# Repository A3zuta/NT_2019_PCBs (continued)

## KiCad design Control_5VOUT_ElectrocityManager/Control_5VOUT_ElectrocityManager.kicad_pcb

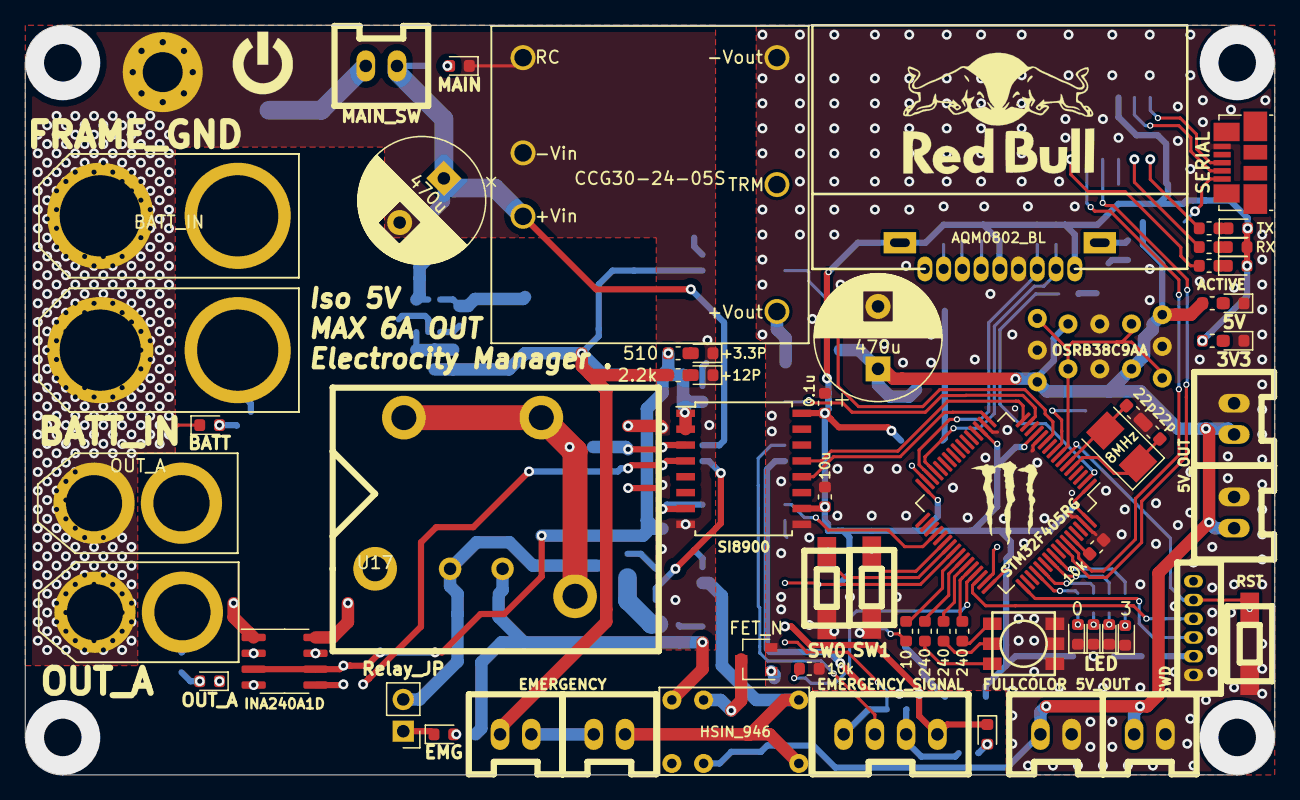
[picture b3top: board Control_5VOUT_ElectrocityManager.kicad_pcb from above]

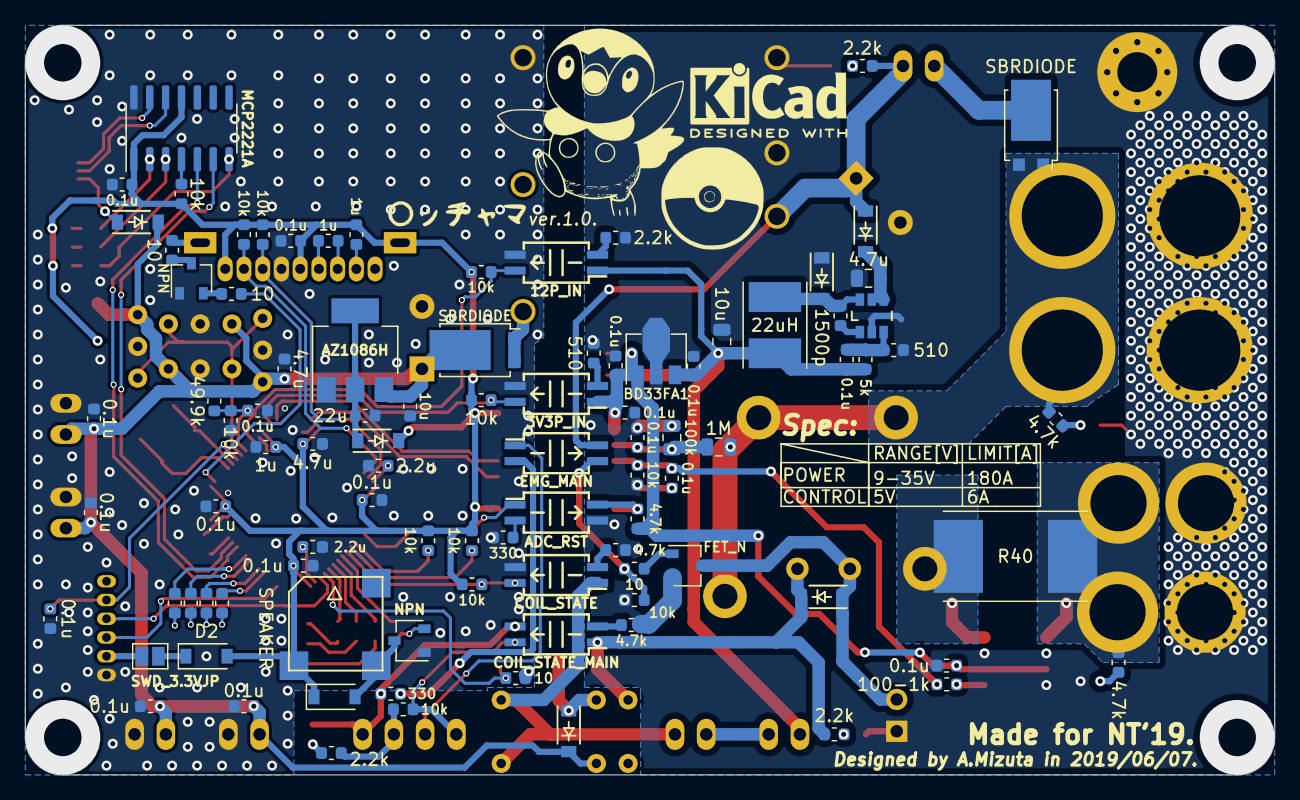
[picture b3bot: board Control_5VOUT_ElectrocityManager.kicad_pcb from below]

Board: 2 copper layers, 100.0 x 60.0 mm, 171 parts (100 on the bottom side), 107 nets.

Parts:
C1, C2: 22p; C_0603_1608Metric
C3, C5, C7, C9, C10, C12, C18, C19, C21, C24, C25, C27, C30, C31, C32, C34, C35, C36, C37: 0.1u; C_0603_1608Metric
C4, C6: 470u; CP_Radial_D10.0mm_P5.00mm
C8, C17: 4.7u; C_0603_1608Metric
C11, C13: 2.2u; C_0603_1608Metric
C14, C26: 10u; C_0603_1608Metric
C15, C22, C23: 1u; C_0603_1608Metric
C16: 22u; C_0603_1608Metric
C28: 1500p; C_0603_1608Metric
C29: 4.7u; C_0805_2012Metric
C33: 10u; C_0805_2012Metric
D1, D2: DIODE; D_SOD-123
D3: TX; LED_0603_1608Metric
D4: RX; LED_0603_1608Metric
D5: ACTIVE; LED_0603_1608Metric
D6, D9: SBRDIODE; TO-277B
D7, D8, D10, D17, D19, D20: DIODE; SOD-123
D11: LED0; LED_0603_1608Metric
D12: LED1; LED_0603_1608Metric
D13: LED2; LED_0603_1608Metric
D14: LED3; LED_0603_1608Metric
D15: 5V; LED_0603_1608Metric
D16: 3V3; LED_0603_1608Metric
D18: MAIN; LED_0603_1608Metric
D21: +3.3P; LED_0603_1608Metric
D22: +12P; LED_0603_1608Metric
D23: BATT; LED_0603_1608Metric
D24: LED; LED_0603_1608Metric
D25: EMG; LED_0603_1608Metric
D26: OUT_A; LED_0603_1608Metric
JP1: SWD_3.3VJP; SolderJumper-2_P1.3mm_Open_Pad1.0x1.5mm
JP2: Relay_JP; PinHeader_1x02_P2.54mm_Vertical
L1: 22uH; L_Taiyo-Yuden_NR-50xx_HandSoldering
LOGO1: OPEN_HARDWARE_1; KiCad-Logo2_5mm_SilkScreen
P1: SWD; ZH_6P
P2: SERIAL; USB_Micro-B_Molex_47346-0001
P3, P5: BATT_IN; XT90PB
P4, P6: OUT_A; XT60_F
P7: MAIN_SW; XA_2P
P8, P9: EMERGENCY; XA_2P
P10: EMERGENCY_SIGNAL; XA_4P
P11: FRAME_GND; MountingHole_3.2mm_M3_Pad_Via
P12, P13, P14, P15: 5V_OUT; XA_2P
Q1, Q4: NPN; SOT-23W
Q2, Q3: FET_N; SOT-23W
R1, R10, R13, R16, R18: 10; R_0603_1608Metric
R2, R32, R47, R48: 510; R_0603_1608Metric
R3, R6, R9, R11, R12, R14, R15, R23, R30, R33, R35, R43, R46, R51: 10k; R_0603_1608Metric
R4, R5, R7, R17, R19, R22, R24, R26, R31, R36: 330; R_0603_1608Metric
R8: 49.9k; R_0603_1608Metric
R20, R37, R39, R49, R52: 2.2k; R_0603_1608Metric
R21, R25, R41, R50, R53: 4.7k; R_0603_1608Metric
R27, R28, R29: 240; R_0603_1608Metric
R34: 5k; R_0603_1608Metric
R40: R; R_Shunt_Vishay_WSR2_WSR3
R42: 100-1k; R_0603_1608Metric
R44: 1M; R_0805_2012Metric
R45: 100k; R_0805_2012Metric
SP1: SPEAKER; UGCT7525AN4
SW1: RESET; SMD_Button
SW2: SW0; SMD_Button
SW3: SW1; SMD_Button
U1: CCG30-24-05S; CCG30-24-xxS
U2: MCP2221A; SOIC-14_3.9x8.7mm_P1.27mm
U3: STM32F405RG; LQFP-64_10x10mm_P0.5mm
U4: AZ1086H; SOT-223-3_TabPin2
U5, U7, U9: OSRB38C9AA-Miz; OSRB38C9AA
U6: OSRB38C9AA
U8: HSIN_946; relay_HSINDA_Y14H
U10: EMG_MAIN; SOIJ-4_5.3x5.3mm_Pitch1.27mm
U11: ADC_RST; SOIJ-4_5.3x5.3mm_Pitch1.27mm
U12: AQM0802_BL; AQM0802_BackLight
U13: 12P_IN; SOIJ-4_5.3x5.3mm_Pitch1.27mm
U14: COIL_STATE; SOIJ-4_5.3x5.3mm_Pitch1.27mm
U15: SI8900; Si8900
U16: FULLCOLOR; OSTBABS4C2B
U17: RELAY; V23076-A3001-D142
U18: LOGO; Power_logo_Silk_5x5
U19: BD9G101G; TSOT-6-MK06A
U20: BD33FA1; SOT-89-3
U21: INA240A1D; SOIC-8_3.9x4.9mm_P1.27mm
U22: COIL_STATE_MAIN; SOIJ-4_5.3x5.3mm_Pitch1.27mm
U23: LOGO; Mini_Monster
U24: LOGO; MonsterBall_10x10_silk
U25: LOGO; Pochama_15x15_silk
U26: 3V3P_IN; SOIJ-4_5.3x5.3mm_Pitch1.27mm
U27: LOGO; Pochama_moji_12.9x3.8_silk
U28: LOGO; NT_2019_Logo_10.0x10.0_Mask
U29: LOGO; RedBull_Logo_Silk_16x16
Y1: 8MHz; Crystal_SMD_5032-2Pin_5.0x3.2mm

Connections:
4CellOUT: C4.1, D19.1, P7.2, R37.1, U1.3, U10.4
+3.3VP: C24.1, C30.1, C31.2, R21.1, R48.1, U15.1, U15.2, U20.1, U21.3, U21.6, U26.1
+3V3: C5.1, C8.2, C9.2, C10.2, C12.2, C15.2, C21.2, C22.2, C26.2, C32.2, D1.1, D2.1, D3.2, D4.2, D5.2, D8.2, R6.2, R12.1, R14.1, R23.1, R30.1, R33.1, R35.1, R36.2, R51.1, SP1.1, U2.1, U2.11, U3.1, U3.13, U3.19, U3.32, U3.48, U3.64, U12.5, U12.9, U12.10, U15.10, U15.16
+5V: C6.1, C14.1, C17.2, C18.2, C19.2, C36.2, C37.2, D6.3, D7.2, D10.2, P12.2, P13.2, P14.2, P15.2, R2.2, R8.1, U4.3, U5.3, U6.3, U7.3, U8.2, U9.3
+12P: C25.2, C27.1, C33.1, L1.2, P8.2, R34.2, R49.1, U13.1, U20.3
+BATT: D9.1, D9.2, P3.2, P5.2, R44.1, R50.1, U17.4
/ADC12_IN11: C7.1, R8.2, R9.1, U3.9
/Coil: D20.2, R52.1, U8.4, U17.2, U22.1
/Coil_Out: D20.1, JP2.2, Q3.3, U17.1
/Current_A: C35.1, R42.1, R46.2, U15.4
/D+: P2.3, U2.13
/D-: P2.2, U2.12
/I2C2_SCL: R12.2, U3.29, U12.8
/I2C2_SDA: R14.2, U3.30, U12.7
/OSC_IN: C1.1, U3.5, Y1.1
/OSC_OUT: C2.1, U3.6, Y1.2
/PA1: R51.2, U3.15, U26.4
/PA12: R10.1, R11.2, U3.45
/PB3: R24.1, U3.55
/PB4: R22.1, U3.56
/PB15: U3.36, U11.1
/PC0: U3.8, U5.1, U6.1, U7.1, U9.1
/PC3: R23.2, U3.11, U13.4
/PC7: R35.2, SW3.2, U3.38
/PC8: R33.2, SW2.2, U3.39
/PC9: R30.2, U3.40, U14.4
/PC11: R31.1, U3.52
/PC12: R26.1, U3.53
/PC13: R16.2, U3.2
/SWCLK: P1.3, U3.49
/SWDIO: P1.4, U3.46
/TIM1_CH1: R1.2, U3.41
/TIM1_CH2: R29.2, U3.42
/TIM1_CH3: R28.2, U3.43
/TIM1_CH4: R27.2, U3.44
/USART1_RX: U2.6, U3.59
/USART1_TX: U2.5, U3.58
/USART2_RX: U3.17, U15.12
/USART2_TX: U3.16, U15.13
/Voltage: C34.1, R44.2, R45.1, U15.3
/main_relayRead: P10.4, R43.2, U22.4
/main_shutdown: P10.3, U10.1
/~NRST: C3.2, P1.5, SW1.1, U3.7
COIL_READ: P9.1, U8.1, U14.1
GND: C1.2, C2.2, C3.1, C5.2, C6.2, C7.2, C8.1, C9.1, C10.1, C11.2, C12.1, C13.2, C14.2, C15.1, C16.2, C17.1, C18.1, C19.1, C21.1, C26.1, C32.1, C36.1, C37.1, D11.1, D12.1, D13.1, D14.1, D15.1, D16.1, P1.1, P2.5, P12.1, P13.1, P14.1, P15.1, Q1.1, Q2.2, Q4.1, R3.2, R9.2, R11.1, R17.2, SW1.2, SW2.1, SW3.1, U1.4, U2.14, U3.12, U3.18, U3.63, U4.1, U5.2, U6.2, U7.2, U9.2, U12.6, U13.3, U14.3, U15.9, U16.4, U16.5, U16.6, U26.3
GNDPWR: C4.2, C24.2, C27.2, C29.2, C30.2, C31.1, C33.2, C34.2, C35.2, D17.1, D18.1, D21.1, D22.1, D23.1, D25.1, D26.1, JP2.1, P3.1, P4.1, P5.1, P6.1, P11.1, Q3.2, R15.2, R20.2, R25.2, R32.2, R41.2, R45.2, R46.1, R47.2, U1.1, U1.2, U11.3, U15.8, U19.2, U20.2, U21.2, U21.4, U21.7
GNDREF: D24.1, P10.1, R19.2, U22.3
Main_Vdd: P10.2, R39.2, R43.1
unnamed: C11.1, U3.31
unnamed: C13.1, U3.47
unnamed: C16.1, D8.1, U4.2
unnamed: C22.1, U12.2
unnamed: C23.1, U12.3
unnamed: C23.2, U12.4
unnamed: C25.1, R32.1, R34.1, U19.3
unnamed: C28.1, D17.2, L1.1, U19.6
unnamed: C28.2, U19.1
unnamed: C29.1, D19.2, U19.4, U19.5
unnamed: D1.2, Q1.3, SP1.2
unnamed: D2.2, JP1.1
unnamed: D3.1, R4.2
unnamed: D4.1, R5.2
unnamed: D5.1, R7.2
unnamed: D6.1, D6.2, U1.6
unnamed: D7.1, P2.1
unnamed: D9.3, P7.1
unnamed: D10.1, Q2.3, U8.5
unnamed: D11.2, R22.2
unnamed: D12.2, R24.2
unnamed: D13.2, R26.2
unnamed: D14.2, R31.2
unnamed: D15.2, R2.1
unnamed: D16.2, R36.1
unnamed: D18.2, R37.2
unnamed: D21.2, R48.2
unnamed: D22.2, R49.2
unnamed: D23.2, R50.2
unnamed: D24.2, R39.1
unnamed: D25.2, R52.2
unnamed: D26.2, R53.2
unnamed: JP1.2, P1.2
unnamed: P8.1, P9.2
unnamed: Q1.2, R1.1
unnamed: Q2.1, R10.2
unnamed: Q3.1, R13.2
unnamed: Q4.2, R16.1
unnamed: Q4.3, R18.2
unnamed: R3.1, U3.60
unnamed: R4.1, U2.2
unnamed: R5.1, U2.3
unnamed: R6.1, U2.4
unnamed: R7.1, U2.7
unnamed: R13.1, R15.1, U10.3
unnamed: R17.1, U11.2
unnamed: R18.1, U12.11
unnamed: R19.1, U10.2
unnamed: R20.1, U13.2
unnamed: R21.2, U11.4, U15.7
unnamed: R25.1, U14.2
unnamed: R27.1, U16.1
unnamed: R28.1, U16.2
unnamed: R29.1, U16.3
unnamed: R40.1, U17.5, U21.8
unnamed: R41.1, U22.2
unnamed: R42.2, U21.5
unnamed: R47.1, U26.2
OUTA: P4.2, P6.2, R40.2, R53.1, U21.1

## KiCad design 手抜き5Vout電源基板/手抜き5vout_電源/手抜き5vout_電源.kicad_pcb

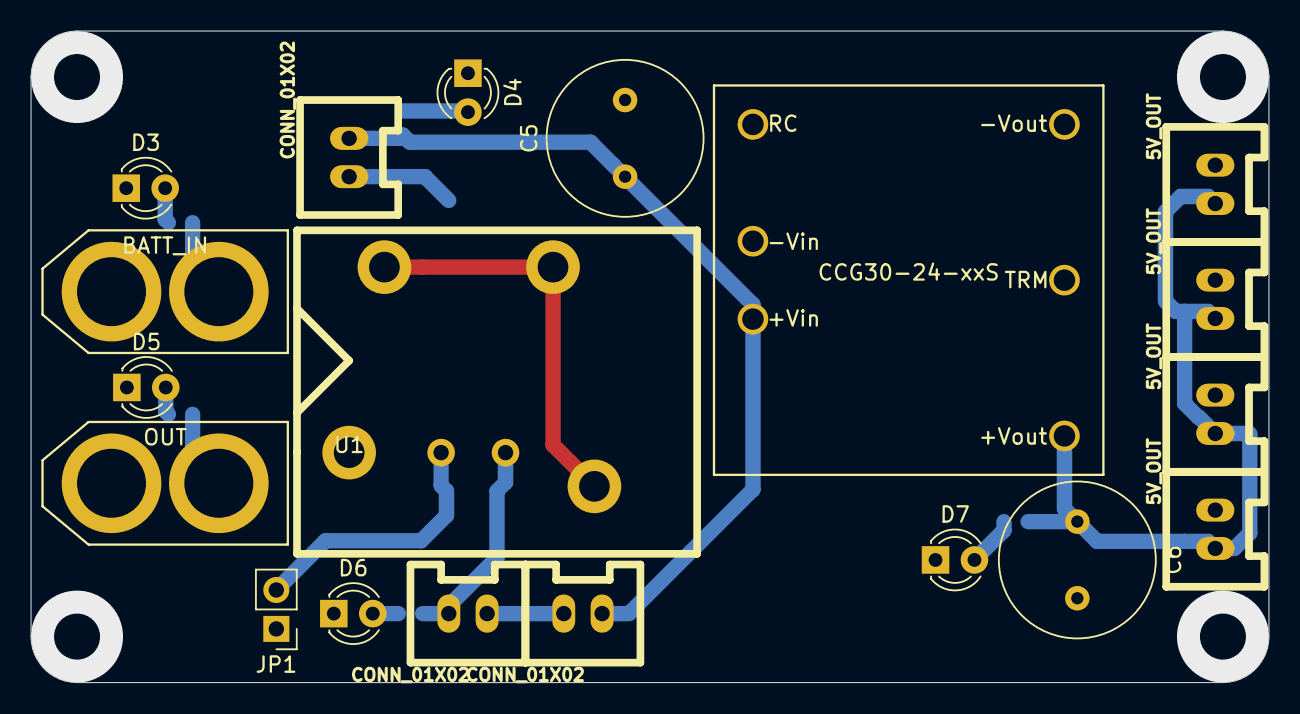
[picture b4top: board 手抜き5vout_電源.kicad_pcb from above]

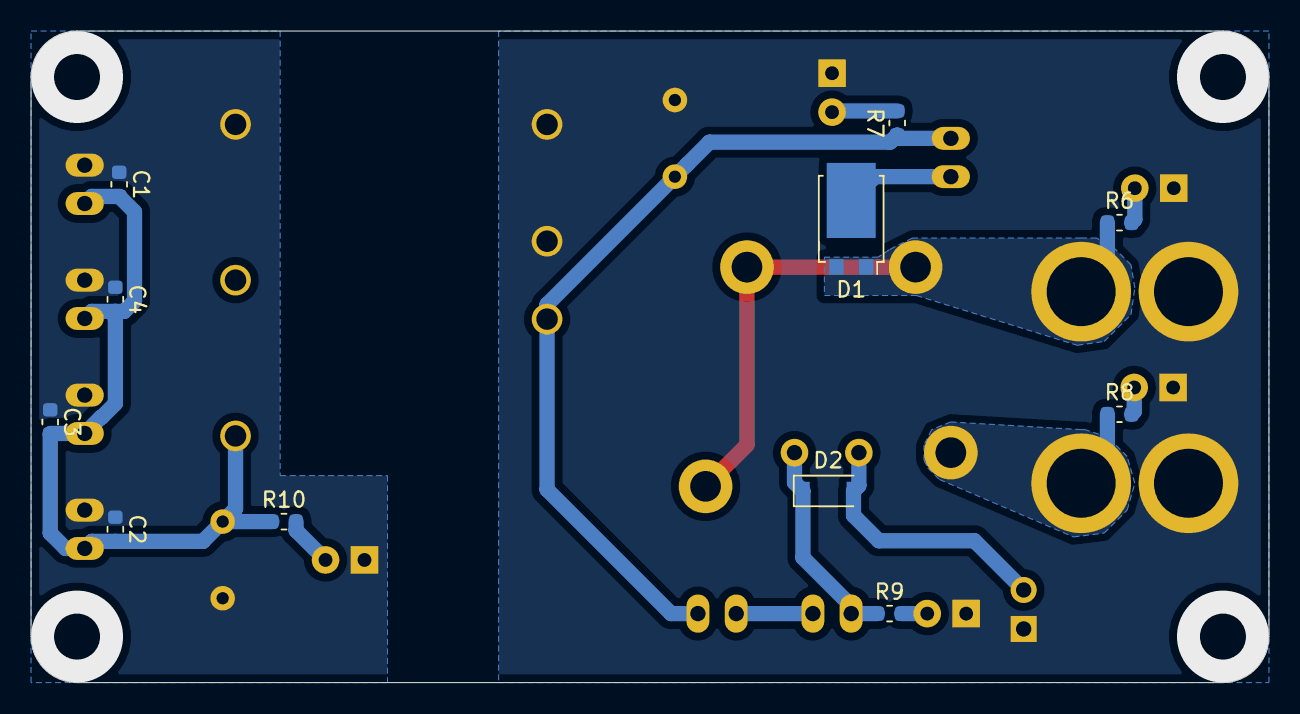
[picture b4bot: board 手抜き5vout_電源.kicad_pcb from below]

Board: 2 copper layers, 80.8 x 42.5 mm, 30 parts (11 on the bottom side), 15 nets.

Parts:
C1, C2, C3, C4: C; C_0603_1608Metric
C5, C6: 470u; C_Radial_D10.0mm_H16.0mm_P5.00mm
D1: SBRDIODE; TO-277B
D2: DIODE; D_SOD-123
D3, D4, D5, D6, D7: LED; LED_D3.0mm
JP1: Relay_JP; PinHeader_1x02_P2.54mm_Vertical
P1: OUT; XT60_F
P2, P3, P6, P7: 5V_OUT; XA_2P
P4: BATT_IN; XT60_M
P5, P8, P9: CONN_01X02; XA_2P
R6, R7, R8, R9, R10: R; R_0603_1608Metric
U1: RELAY; V23076-A3001-D142
U2: CCG30-24-xxS

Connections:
+5V: C1.2, C2.2, C3.2, C4.2, C6.1, P2.2, P3.2, P6.2, P7.2, R10.1, U2.6
+BATT: D1.1, D1.2, P4.2, R6.1, U1.4
Coil: D2.1, P9.1, R9.1, U1.2
GND: C1.1, C2.1, C3.1, C4.1, C6.2, D7.1, P2.1, P3.1, P6.1, P7.1, U2.4
GNDPWR: C5.2, D3.1, D4.1, D5.1, D6.1, JP1.1, P1.1, P4.1, U2.1, U2.2
unnamed: D1.3, P5.2
unnamed: D2.2, JP1.2, U1.1
unnamed: D3.2, R6.2
unnamed: D4.2, R7.2
unnamed: D5.2, R8.2
unnamed: D6.2, R9.2
unnamed: D7.2, R10.2
unnamed: P8.1, P9.2
OUT: P1.2, R8.1, U1.5
batt+: C5.1, P5.1, P8.2, R7.1, U2.3

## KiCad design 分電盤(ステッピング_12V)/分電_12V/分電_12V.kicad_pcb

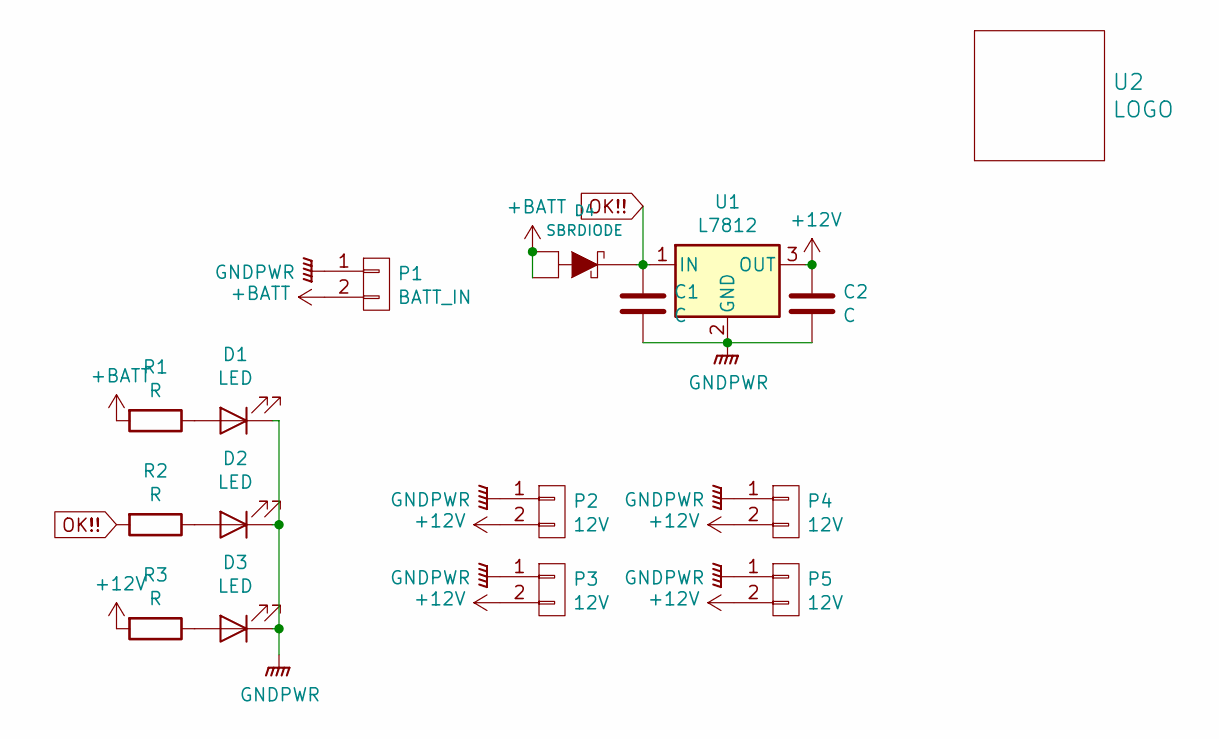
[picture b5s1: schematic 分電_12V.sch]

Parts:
C1, C2: C; C_0603_1608Metric
D1, D2, D3: LED; LED_D3.0mm
D4: SBRDIODE; TO-277B
P1: BATT_IN; XT60_F
P2, P3, P4, P5: 12V; XA_2P
R1, R2, R3: R; R_0603_1608Metric
U1: L7812; TO-252-2
U2: LOGO; Hikozaru_15x15_silk

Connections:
+12V: C2.1, P2.2, P3.2, P4.2, P5.2, R3.2, U1.3 (OUT)
+BATT: D4.1 (A), D4.2 (A), P1.2, R1.2
GNDPWR: C1.2, C2.2, D1.1 (K), D2.1 (K), D3.1 (K), P1.1, P2.1, P3.1, P4.1, P5.1, U1.2 (GND)
unnamed: D1.2 (A), R1.1
unnamed: D2.2 (A), R2.1
unnamed: D3.2 (A), R3.1
OK!!: C1.1, D4.3 (K), R2.2, U1.1 (IN)

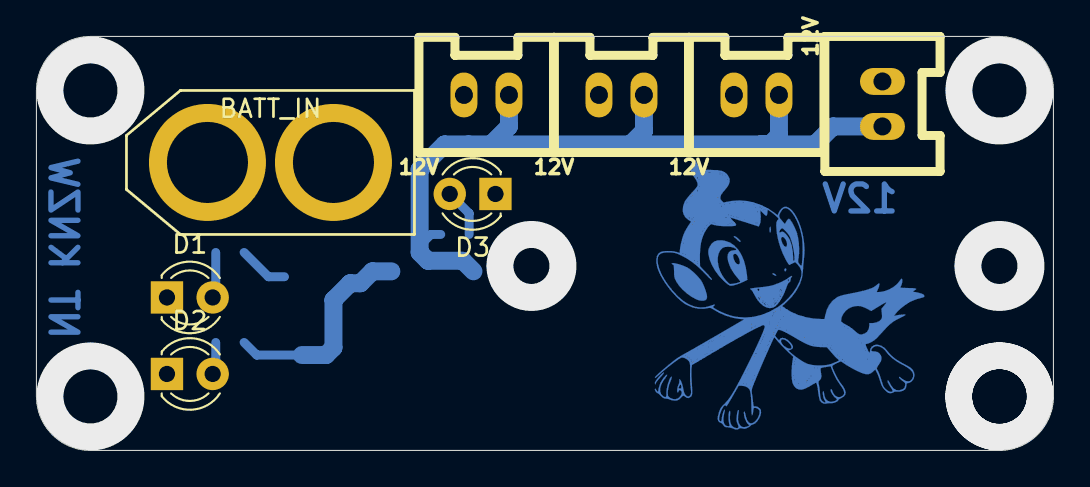
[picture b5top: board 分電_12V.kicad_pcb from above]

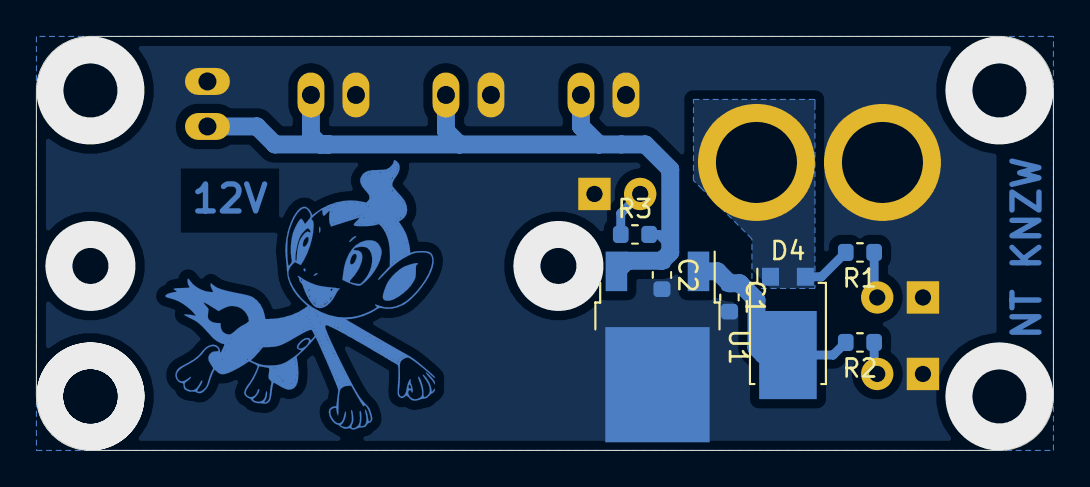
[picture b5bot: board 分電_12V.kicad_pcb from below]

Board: 2 copper layers, 56.5 x 23.0 mm, 16 parts (8 on the bottom side), 7 nets.

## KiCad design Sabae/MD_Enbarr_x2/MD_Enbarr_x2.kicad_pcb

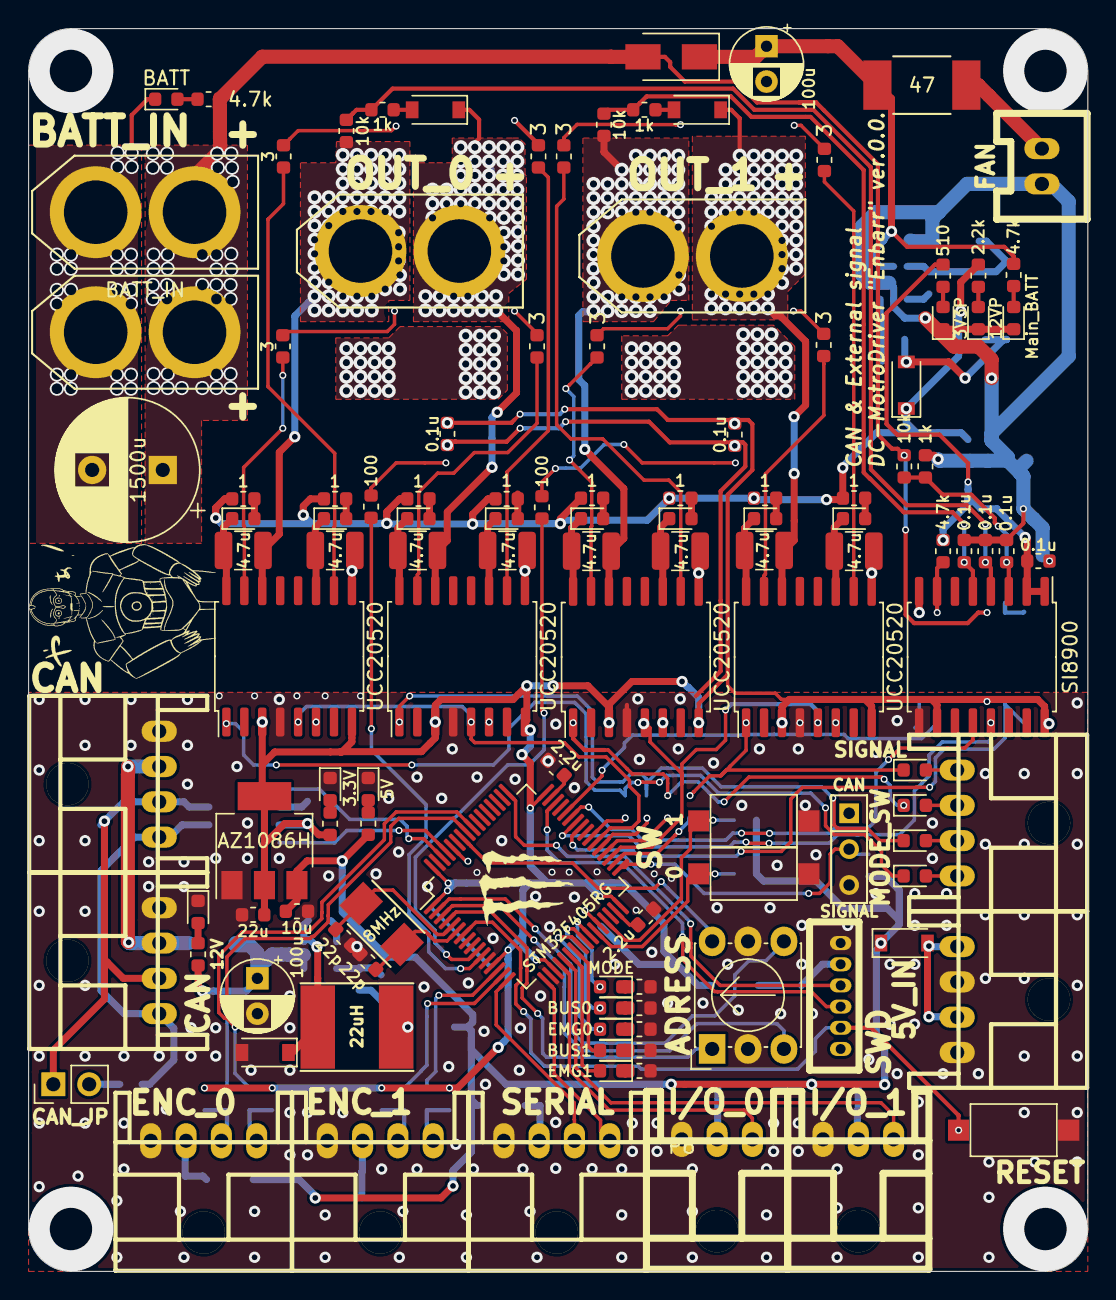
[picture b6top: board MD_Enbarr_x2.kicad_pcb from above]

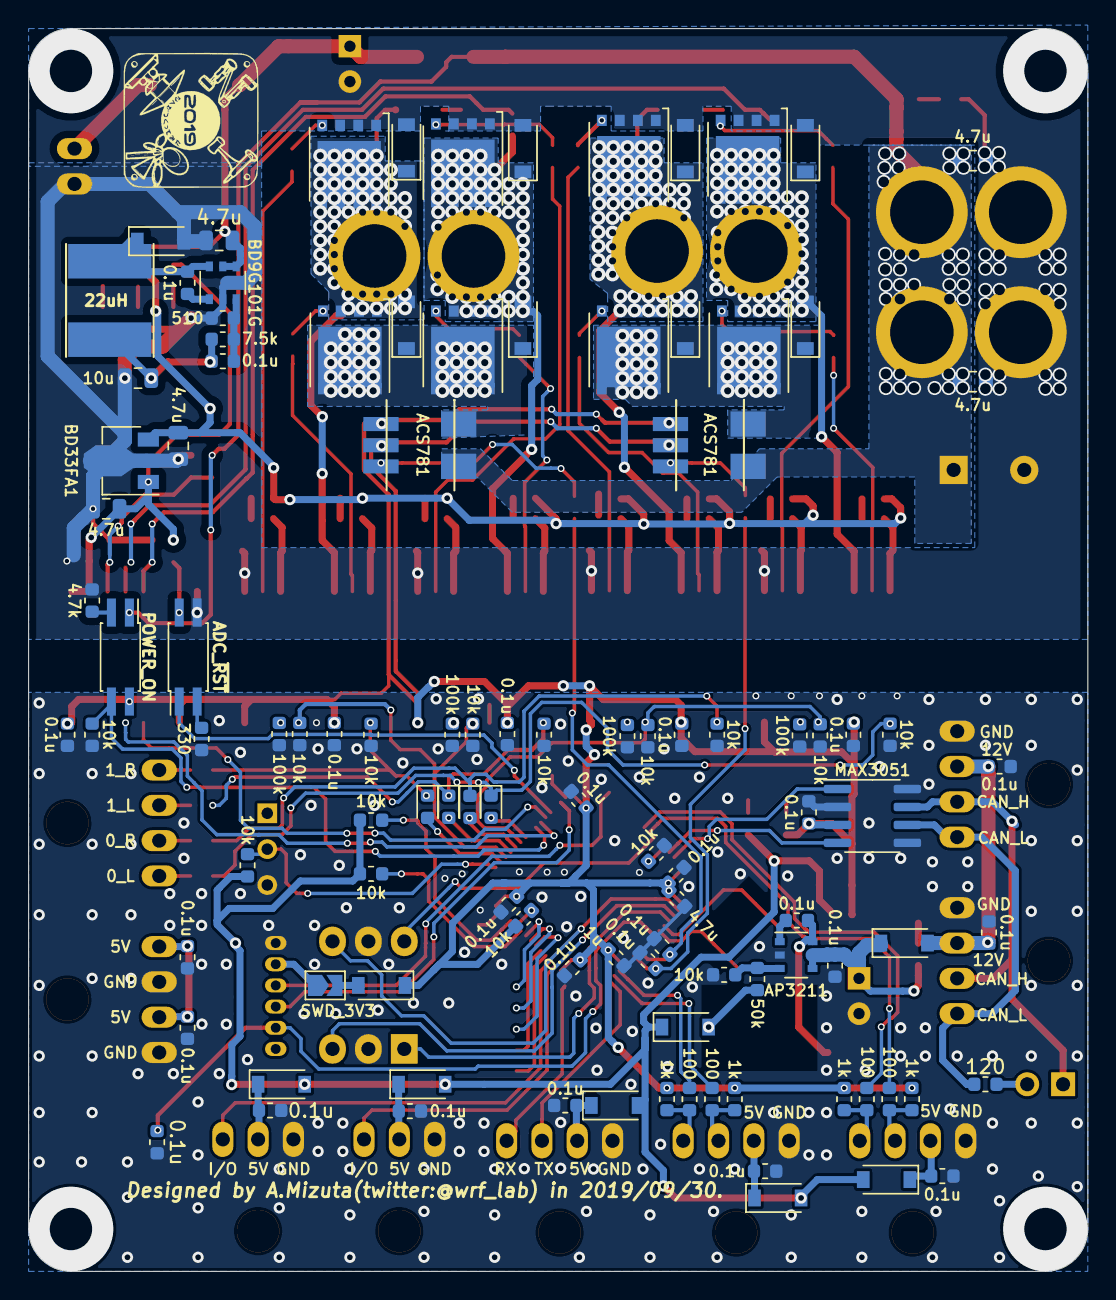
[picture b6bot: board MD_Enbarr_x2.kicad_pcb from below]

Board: 2 copper layers, 75.0 x 88.0 mm, 230 parts (107 on the bottom side), 149 nets.

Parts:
C1, C3: 22p; C_0603_1608Metric
C2, C4, C5, C6, C7, C8, C9, C11, C15, C16, C17, C18, C21, C22, C23, C24, C26, C27, C36, C38, C39, C40, C41, C42, C44, C45, C46, C49, C50, C51, C54, C55: 0.1u; C_0603_1608Metric
C10: 1u; C_0603_1608Metric
C12: 4.7u; C_0603_1608Metric
C13, C14: 2.2u; C_0603_1608Metric
C19, C20, C30, C31, C47, C48, C52, C53: 4.7u; C_1210_3225Metric
C25, C33: 100u; CP_Radial_D5.0mm_P2.50mm
C28: 10u; C_0805_2012Metric
C29, C32, C35, C37, C43: 4.7u; C_0805_2012Metric
C34: 1500u; CP_Radial_D10.0mm_P5.00mm
C56: 10u; C_0603_1608Metric
C57: 22u; C_0603_1608Metric
D1, D4, D5, D6, D10, D16, D17, D18, D24, D25, D26, D28, D29, D30, D31, D38, D45, D46, D47, D48, D49, D52: DIODE; D_SOD-123
D2, D3, D12, D13, D14, D19, D20, D35, D36, D37, D41, D42, D43, D44, D50, D51: DIODE; D_0603_1608Metric
D7: EMG1; LED_0603_1608Metric
D8: BUS1; LED_0603_1608Metric
D9: EMG0; LED_0603_1608Metric
D15: DIODE; D_SMA
D21: BATT; LED_0603_1608Metric
D22: 12VP; LED_0603_1608Metric
D23: 3V3P; LED_0603_1608Metric
D27: Main_BATT; LED_0603_1608Metric
D32: 12V; LED_0603_1608Metric
D33: 5V; LED_0603_1608Metric
D34: 3.3V; LED_0603_1608Metric
D39: BUS0; LED_0603_1608Metric
D40: MODE; LED_0603_1608Metric
JP1: SWD_3V3; SolderJumper-2_P1.3mm_Open_TrianglePad1.0x1.5mm
JP2: CAN_JP; PinHeader_1x02_P2.54mm_Vertical
L1, L2: 22uH; Inductor_Taiyo-Yuden_NR-60xx_HandSoldering
P1: SWD; ZH_6P
P2: 5V_IN; XA_4LC
P3, P4: CAN; XA_4LC
P5: SERIAL; XA_4LC
P6: I/O_0; XA_3LC
P7: FAN; XA_2P
P8: BATT_IN; XT60_M
P9: BATT_IN; XT60_F
P10: OUT_1; XT60_F
P11: ENC_0; XA_4LC
P12: SIGNAL; XA_4LC
P13: ENC_1; XA_4LC
P14: I/O_1; XA_3LC
P15: OUT_0; XT60_F
Q1, Q2, Q3, Q4, Q5, Q6, Q7, Q8: BSC014N06; TDSON-8-1
R1, R2, R4, R5, R9, R10, R22, R26, R36, R38, R39, R53, R61, R68, R69, R70, R71, R72: 10k; R_0603_1608Metric
R3: 120; R_0603_1608Metric
R6, R7, R8, R12, R49, R51, R52: 330; R_0603_1608Metric
R11, R35, R54, R67: 100k; R_0603_1608Metric
R14: 7.5k; R_0603_1608Metric
R15, R34, R48: 510; R_0603_1608Metric
R16, R32, R40, R41: 4.7k; R_0603_1608Metric
R17, R18, R30, R31, R55, R56, R65, R66: 3; R_0603_1608Metric
R19, R20, R28, R29, R58, R59, R63, R64: 1; R_0603_1608Metric
R21, R23, R24, R27, R42, R43, R62: 1k; R_0603_1608Metric
R25: 47; R_2812
R33: 2.2k; R_0603_1608Metric
R37: 50k; R_0603_1608Metric
R44, R45, R46, R50, R57, R60: 100; R_0603_1608Metric
R47: 1.2k; R_0603_1608Metric
SW1: RESET; SW_SPST_CK_RS282G05A3
SW2: MODE_SW; SW_Micro_SPST
SW3: SW0; SW_SPST_CK_RS282G05A3
SW4: SW1; SW_SPST_CK_RS282G05A3
SW5: ADRESS; Nidec_Copal_SH-7010C
U1: MAX3051; SOIC-8_3.9x4.9mm_P1.27mm
U2: AP3211; TSOP-6_1.65x3.05mm_P0.95mm
U3: STM32F405RG; LQFP-64_10x10mm_P0.5mm
U4, U8, U10, U14: UCC20520; SOIC-16W_7.5x10.3mm_P1.27mm
U5: SI8900; SOIC-16W_7.5x10.3mm_P1.27mm
U6: ADC_~RST; SO-4_4.4x2.3mm_P1.27mm
U7: BD9G101G; TSOP-6_1.65x3.05mm_P0.95mm
U9: BD33FA1; SOT-89-3
U11: POWER_ON; SO-4_4.4x2.3mm_P1.27mm
U12, U13: ACS781; ACS781_No_side_mask
U15: AZ1086H; SOT-223-3_TabPin2
U16: LOGO; Mini_Monster
U17: LOGO; C3PO_silk_11.3x15.0
U18: LOGO; NT_2019_Logo_10.0x10.0_Silk
Y1: 8MHz; Crystal_SMD_5032_2Pads

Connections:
+3.3VP: C22.1, C32.1, R16.1, R34.2, U5.1, U5.2, U9.1
+3V3: C5.1, C6.1, C8.1, C9.1, C10.1, C12.1, C17.1, C36.1, C40.1, C41.1, C42.1, C45.1, C46.1, C54.1, C57.1, D4.1, R9.1, R21.1, R24.1, R42.1, R43.1, R49.2, U1.3, U3.1, U3.13, U3.19, U3.32, U3.48, U3.64, U4.3, U4.8, U5.10, U5.16, U8.3, U8.8, U10.3, U10.8, U11.4, U12.1, U13.1, U14.3, U14.8, U15.2
+5V: C56.1, D1.1, D6.2, D10.2, D26.1, D28.2, D38.2, D52.2, R2.1, R4.1, R5.1, R48.2, U15.3
+12P: C29.1, D18.1, R19.1, R20.1, R28.1, R29.1, R33.2, R58.1, R59.1, R63.1, R64.1, U9.3
+12V: C33.1, C38.1, D5.1, R47.2, U2.4, U2.5
+BATT: C34.1, C35.1, C43.1, D15.2, P8.2, P9.2, R22.1, R32.2, U11.1, U12.5, U13.5
/ADC_~RST: R16.2, U5.7, U6.4
/ADR_1: SW5.1, U3.4
/ADR_2: SW5.2, U3.2
/ADR_4: SW5.4, U3.3
/ADR_8: SW5.8, U3.58
/CAN1_RX: U1.4, U3.61
/CAN1_TX: U1.1, U3.62
/CAN_H: JP2.1, P3.3, P4.3, U1.7
/CAN_L: P3.4, P4.4, R3.1, U1.6
/CAN_Vdd: C7.2, C11.2, D5.2, P3.2, P4.2
/CounterVoltage0: C27.1, R26.2, R27.1, U5.4
/CounterVoltage1: C51.1, R61.2, R62.1, U5.5
/Current0: C50.1, R60.2, U3.11
/Current1: C49.1, R57.2, U3.10
/EN0: R10.1, R36.1, U3.38, U4.5, U10.5
/EN1: R53.1, R68.1, U3.35, U8.5, U14.5
/FB: R37.2, R38.1, U2.3
/FB_PWR: C18.2, R14.2, R15.1, U7.3
/FB_PWR_OUT: C18.1, C28.1, D18.2, L1.2, R14.1
/LED0: D7.2, U3.22
/LED1: D8.2, U3.23
/LED2: D9.2, U3.24
/LED3: D39.2, U3.25
/LED4: D40.2, U3.26
/MODE: R2.2, SW2.2, U3.33
/MOTOR0_BATT: D25.1, D30.1, Q1.5, Q3.5, U13.6
/MOTOR1_BATT: D45.1, D48.1, Q5.5, Q7.5, U12.6
/OSC_IN: C1.2, U3.5, Y1.1
/OSC_OUT: C3.2, U3.6, Y1.2
/OUT0_L: C19.2, D25.2, D29.1, P15.1, Q1.1, Q1.2, Q1.3, Q2.5, R26.1, U4.14
/OUT0_R: C30.2, D17.1, D30.2, D31.1, P15.2, Q3.1, Q3.2, Q3.3, Q4.5, U10.14
/OUT1_L: C47.2, D45.2, D46.1, P10.1, Q5.1, Q5.2, Q5.3, Q6.5, R61.1, U8.14
/OUT1_R: C52.2, D47.1, D48.2, D49.1, P10.2, Q7.1, Q7.2, Q7.3, Q8.5, U14.14
/PA4: P6.3, U3.20
/PA5: P14.3, U3.21
/PA8: R39.1, U3.41, U11.3
/PA11: U3.44, U6.1
/PWM0_L: D2.1, D37.1, R69.1, U4.1
/PWM0_R: D3.1, D36.1, R71.1, U10.1
/PWM1_L: D12.1, D42.1, R70.1, U8.1
/PWM1_R: D35.1, D41.1, R72.1, U14.1
/SW0: R4.2, SW3.2, U3.27
/SW1: R5.2, SW4.2, U3.29
/SWCLK: P1.3, U3.49
/SWDIO: P1.4, U3.46
/TIM3_CH1: R44.2, U3.56
/TIM3_CH2: R45.2, U3.57
/TIM5_CH1: R46.2, U3.14
/TIM5_CH2: R50.2, U3.15
/USART1_RX: U3.43, U5.12
/USART1_TX: U3.42, U5.13
/USART2_RX: P5.4, U3.17
/USART2_TX: P5.3, U3.16
/Voltage: C24.1, R22.2, R23.1, U5.3
/batt: C25.1, C37.1, D15.1, R25.2, R41.2, U7.4, U7.5
/~RST: C2.2, P1.5, SW1.1, U3.7
GND: C1.1, C2.1, C3.1, C4.1, C5.2, C6.2, C7.1, C8.2, C9.2, C10.2, C11.1, C12.2, C13.2, C14.2, C15.1, C16.1, C17.2, C21.1, C26.1, C33.2, C36.2, C38.2, C40.2, C41.2, C42.2, C44.1, C45.2, C46.2, C49.2, C50.2, C54.2, C55.1, C56.2, C57.2, D24.2, D32.1, D33.1, D34.1, P1.1, P2.1, P2.3, P3.1, P4.1, P5.1, P6.1, P11.1, P13.1, P14.1, R1.2, R6.2, R7.2, R8.2, R10.2, R11.2, R12.2, R35.2, R36.2, R38.2, R39.2, R51.2, R52.2, R53.2, R54.2, R67.2, R68.2, R69.2, R70.2, R71.2, R72.2, SW1.2, SW2.3, SW3.1, SW4.1, SW5.C, U1.2, U1.5, U1.8, U2.2, U3.12, U3.18, U3.63, U4.4, U5.9, U8.4, U10.4, U12.2, U13.2, U14.4, U15.1
GNDPWR: C20.2, C22.2, C24.2, C25.2, C27.2, C28.2, C29.2, C31.2, C32.2, C34.2, C35.2, C37.2, C43.2, C48.2, C51.2, C53.2, D16.2, D21.1, D22.1, D23.1, D27.1, D29.2, D31.2, D46.2, D49.2, P7.1, P8.1, P9.1, Q2.1, Q2.2, Q2.3, Q4.1, Q4.2, Q4.3, Q6.1, Q6.2, Q6.3, Q8.1, Q8.2, Q8.3, R15.2, R23.2, R40.2, U4.9, U5.8, U6.3, U7.2, U8.9, U9.2, U10.9, U14.9
unnamed: C13.1, U3.31
unnamed: C14.1, U3.47
unnamed: C15.2, D6.1, P5.2
unnamed: C16.2, D10.1, P6.2
unnamed: C19.1, D13.1, U4.16
unnamed: C20.1, D14.1, U4.11
unnamed: C4.2, C21.2, D1.2, P2.2, P2.4
unnamed: C23.1, D16.1, L1.1, U7.6
unnamed: C23.2, U7.1
unnamed: C26.2, D28.1, P11.2
unnamed: C30.1, D19.1, U10.16
unnamed: C31.1, D20.1, U10.11
unnamed: C39.1, D24.1, L2.1, U2.6
unnamed: C39.2, U2.1
unnamed: C44.2, D38.1, P13.2
unnamed: C47.1, D43.1, U8.16
unnamed: C48.1, D44.1, U8.11
unnamed: C52.1, D50.1, U14.16
unnamed: C53.1, D51.1, U14.11
unnamed: C55.2, D52.1, P14.2
unnamed: D2.2, P12.1
unnamed: D3.2, P12.2
unnamed: D4.2, JP1.2
unnamed: D7.1, R6.1
unnamed: D8.1, R7.1
unnamed: D9.1, R8.1
unnamed: D12.2, P12.3
unnamed: D13.2, R19.2
unnamed: D14.2, R20.2
unnamed: D17.2, R27.2
unnamed: D19.2, R28.2
unnamed: D20.2, R29.2
unnamed: D21.2, R32.1
unnamed: D22.2, R33.1
unnamed: D23.2, R34.1
unnamed: D26.2, L2.2, R37.1
unnamed: D27.2, R41.1
unnamed: D32.2, R47.1
unnamed: D33.2, R48.1
unnamed: D34.2, R49.1
unnamed: D35.2, P12.4
unnamed: D36.2, U3.37
unnamed: D37.2, U3.39
unnamed: D39.1, R51.1
unnamed: D40.1, R52.1
unnamed: D41.2, U3.34
unnamed: D42.2, U3.36
unnamed: D43.2, R58.2
unnamed: D44.2, R59.2
unnamed: D47.2, R62.2
unnamed: D50.2, R63.2
unnamed: D51.2, R64.2
unnamed: JP1.1, P1.2
unnamed: JP2.2, R3.2
unnamed: P7.2, R25.1
unnamed: P11.3, R43.2, R45.1
unnamed: P11.4, R42.2, R44.1
unnamed: P13.3, R24.2, R50.1
unnamed: P13.4, R21.2, R46.1
unnamed: Q1.4, R17.1
unnamed: Q2.4, R18.1
unnamed: Q3.4, R30.1
unnamed: Q4.4, R31.1
unnamed: Q5.4, R55.1
unnamed: Q6.4, R56.1
unnamed: Q7.4, R65.1
unnamed: Q8.4, R66.1
unnamed: R1.1, U3.60
unnamed: R9.2, U3.28
unnamed: R11.1, U4.6
unnamed: R12.1, U6.2
unnamed: R17.2, U4.15
unnamed: R18.2, U4.10
unnamed: R30.2, U10.15
unnamed: R31.2, U10.10
unnamed: R35.1, U10.6
unnamed: R40.1, U11.2
unnamed: R54.1, U8.6
unnamed: R55.2, U8.15
unnamed: R56.2, U8.10
unnamed: R57.1, U12.3
unnamed: R60.1, U13.3
unnamed: R65.2, U14.15
unnamed: R66.2, U14.10
unnamed: R67.1, U14.6

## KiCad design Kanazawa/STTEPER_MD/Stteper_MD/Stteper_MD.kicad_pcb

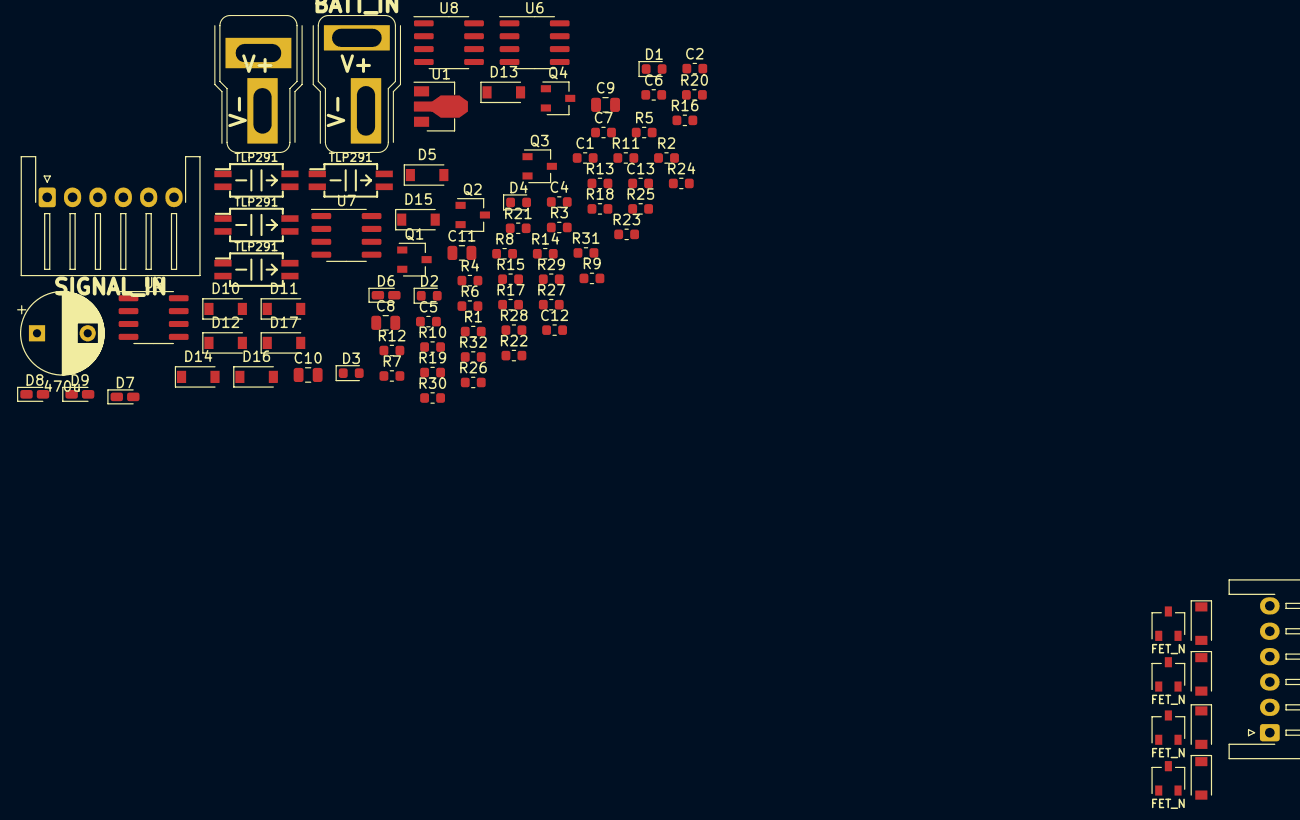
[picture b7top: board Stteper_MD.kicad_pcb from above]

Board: 2 copper layers, 87 parts (0 on the bottom side), 58 nets, no tracks yet.

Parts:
C1, C2, C4, C5, C6, C7, C12, C13: 0.1u; C_0603_1608Metric
C3: 470u; CP_Radial_D8.0mm_P5.00mm
C8, C9, C10, C11: 4.7u; C_0805_2012Metric
D1: BATT; LED_0603_1608Metric
D2: batt+; LED_0603_1608Metric
D3: +12P; LED_0603_1608Metric
D4: 5V; LED_0603_1608Metric
D5, D10, D11, D12, D13, D14, D15, D16, D17, D18, D19, D20, D21: DIODE; D_SOD-123
D6, D7, D8, D9: LED; LED_0603_1608Metric_Castellated
P1: SIGNAL_IN; JST_XH_S6B-XH-A-1_1x06_P2.50mm_Horizontal
P2: BATT_IN; DEANS_T_F_ver.Mizz
P3: BATT_IN; DEANS_T_M_ver.Mizz
P4: OUT; JST_XH_S6B-XH-A-1_1x06_P2.50mm_Horizontal
Q1, Q2, Q3, Q4, Q5, Q6, Q7, Q8: FET_N; SOT-23W
R1, R2: 4.7k; R_0603_1608Metric
R3: 2.2k; R_0603_1608Metric
R4: 510; R_0603_1608Metric
R5, R6, R7, R8: 330; R_0603_1608Metric
R9, R10, R11, R12, R17, R18, R19, R20: 10k; R_0603_1608Metric
R13, R14, R15, R16: 1.2k; R_0603_1608Metric
R21, R22, R23, R24: 1; R_0603_1608Metric
R25, R26, R27, R28, R29, R30, R31, R32: 10; R_0603_1608Metric
U1: NJM78L00; SOT-89-3
U2, U3, U4, U5: TLP291; SOIJ-4_5.3x5.3mm_Pitch1.27mm
U6, U7, U8, U9: IR2104; SOIC-8_3.9x4.9mm_P1.27mm

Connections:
+5V: P1.2, R4.2
+12P: C1.1, C4.1, C5.1, C6.1, C7.1, R3.2, R17.1, R18.1, R19.1, R20.1, R21.2, R22.2, R23.2, R24.2, U1.1, U2.4, U3.4, U4.4, U5.4, U6.1, U7.1, U8.1, U9.1
+BATT: C3.1, D5.2, D14.1, D16.1, D18.1, D20.1, P2.2, P3.2, Q1.3, Q3.3, Q5.3, Q7.3, R1.2
GND: D4.1, P1.1, R5.2, R6.2, R7.2, R8.2
GNDPWR: C1.2, C2.2, C3.2, C4.2, C5.2, C6.2, C7.2, D1.1, D2.1, D3.1, D6.1, D7.1, D8.1, D9.1, D15.2, D17.2, D19.2, D21.2, P2.1, P3.1, Q2.2, Q4.2, Q6.2, Q8.2, R9.2, R10.2, R11.2, R12.2, U1.2, U6.4, U7.4, U8.4, U9.4
unnamed: C8.1, D10.1, U6.8
unnamed: C9.1, D11.1, U7.8
unnamed: C10.1, D12.1, U8.8
unnamed: C11.1, D13.1, U9.8
unnamed: D1.2, R1.1
unnamed: D2.2, R2.1
unnamed: D3.2, R3.1
unnamed: D4.2, R4.1
unnamed: D6.2, R13.1
unnamed: D7.2, R14.1
unnamed: D8.2, R15.1
unnamed: D9.2, R16.1
unnamed: D10.2, R23.1
unnamed: D11.2, R24.1
unnamed: D12.2, R21.1
unnamed: D13.2, R22.1
unnamed: Q1.1, R25.1
unnamed: Q2.1, R26.1
unnamed: Q3.1, R27.1
unnamed: Q4.1, R28.1
unnamed: Q5.1, R29.1
unnamed: Q6.1, R30.1
unnamed: Q7.1, R31.1
unnamed: Q8.1, R32.1
unnamed: R5.1, U2.2
unnamed: R6.1, U3.2
unnamed: R7.1, U4.2
unnamed: R8.1, U5.2
unnamed: R17.2, U6.3
unnamed: R18.2, U7.3
unnamed: R19.2, U8.3
unnamed: R20.2, U9.3
unnamed: R25.2, U6.7
unnamed: R26.2, U6.5
unnamed: R27.2, U7.7
unnamed: R28.2, U7.5
unnamed: R29.2, U8.7
unnamed: R30.2, U8.5
unnamed: R31.2, U9.7
unnamed: R32.2, U9.5
OUT_A: C10.2, C12.1, D18.2, D19.1, P4.1, Q5.2, Q6.3, U8.6
OUT_AN: C11.2, C12.2, D20.2, D21.1, P4.2, Q7.2, Q8.3, U9.6
OUT_B: C8.2, C13.1, D14.2, D15.1, P4.3, Q1.2, Q2.3, U6.6
OUT_BN: C9.2, C13.2, D16.2, D17.1, P4.4, Q3.2, Q4.3, U7.6
PWM_IN0: P1.3, U2.1
PWM_IN1: P1.4, U3.1
PWM_IN2: P1.5, U4.1
PWM_IN3: P1.6, U5.1
PWM_Iso0: R9.1, R13.2, U2.3, U8.2
PWM_Iso1: R10.1, R14.2, U3.3, U9.2
PWM_Iso2: R11.1, R15.2, U4.3, U6.2
PWM_Iso3: R12.1, R16.2, U5.3, U7.2
batt+: C2.1, D5.1, R2.2, U1.3
